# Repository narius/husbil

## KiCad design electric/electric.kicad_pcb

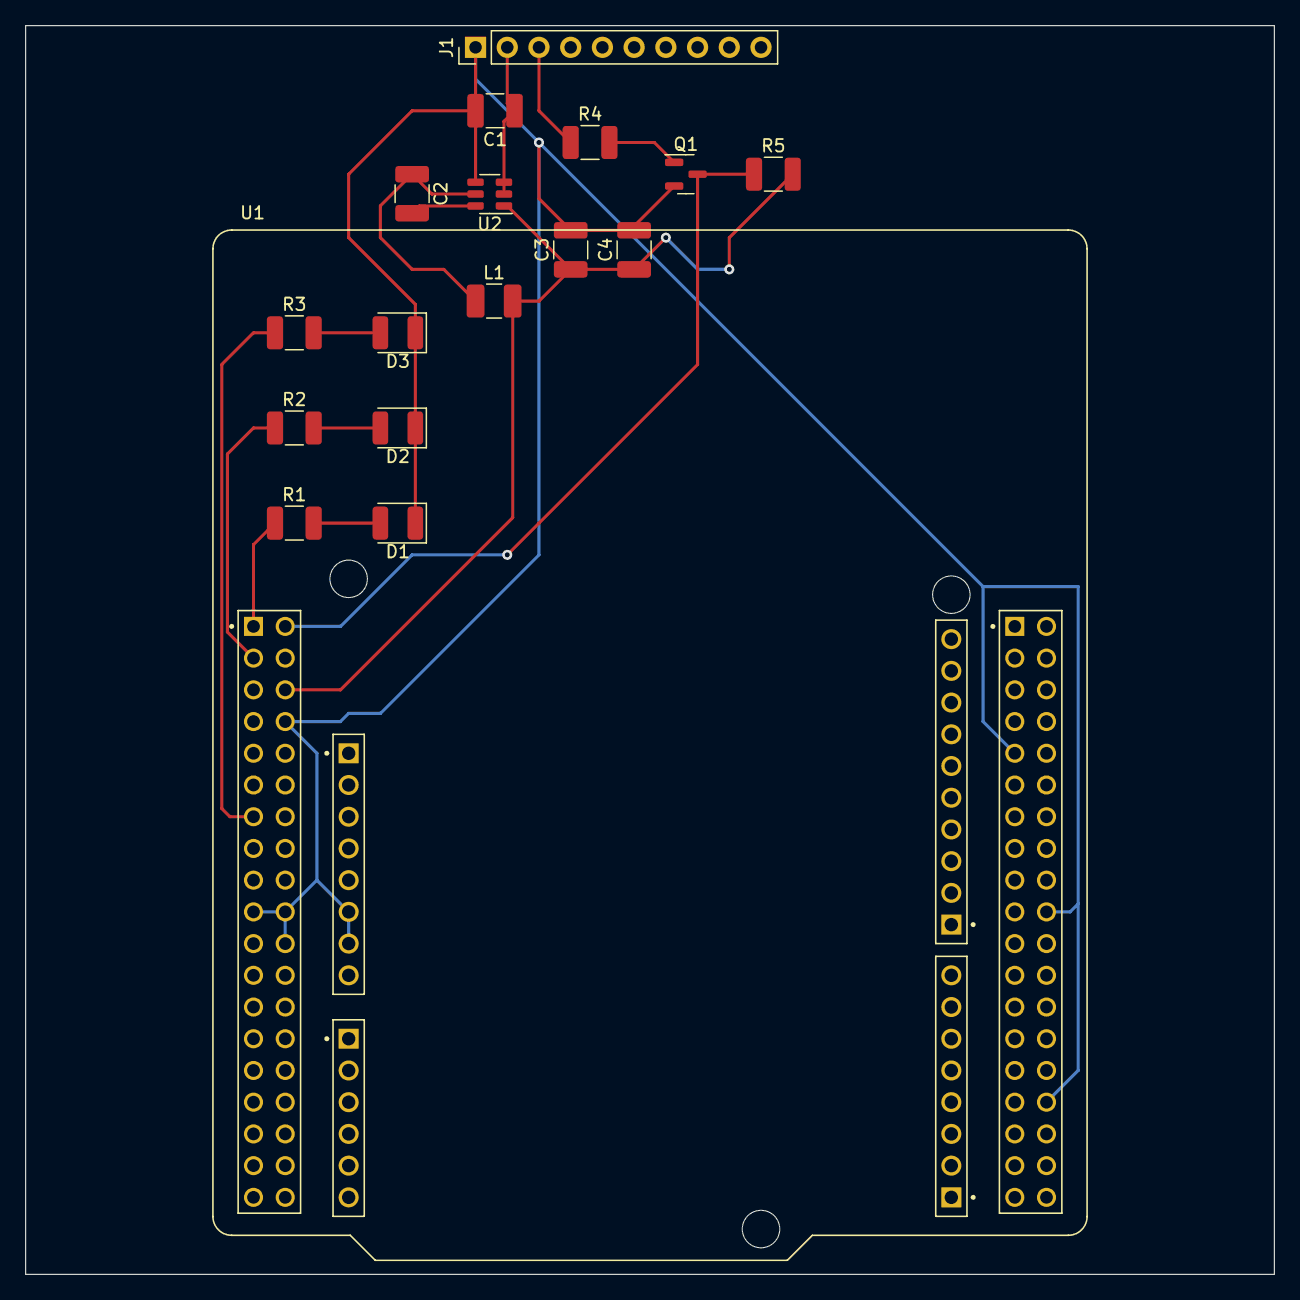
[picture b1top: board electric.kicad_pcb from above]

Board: 2 copper layers, 100.0 x 100.0 mm, 17 parts (0 on the bottom side), 14 nets.

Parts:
C1: 10uF; C_1210_3225Metric_Pad1.33x2.70mm_HandSolder
C2: 100nF; C_1210_3225Metric_Pad1.33x2.70mm_HandSolder
C3, C4: 22uF; C_1210_3225Metric_Pad1.33x2.70mm_HandSolder
D1, D2, D3: LED; LED_1210_3225Metric
J1: Screw_Terminal_01x10; PinHeader_1x10_P2.54mm_Vertical
L1: L; L_1210_3225Metric_Pad1.42x2.65mm_HandSolder
Q1: BSS138; SOT-23
R1, R2, R3, R4, R5: R; R_1210_3225Metric_Pad1.30x2.65mm_HandSolder
U1: NUCLEO-F303RE; ST_NUCLEO-F303RE
U2: AP63205WU; TSOT-23-6

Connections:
12V_IN: C1.1, J1.2, U2.2 (EN), U2.3 (IN)
E5V: C3.1, C4.1, L1.2, R5.2, U1.CN7_6 (E5V), U2.1 (FB)
GND: C1.2, C3.2, C4.2, D1.1 (K), D2.1 (K), D3.1 (K), J1.1, Q1.2 (S), U1.CN6_6 (GND), U1.CN6_7 (GND), U1.CN7_8 (GND_S1), U1.CN7_19 (GND_S1), U1.CN7_20 (GND_S1), U1.CN7_22 (GND_S1), U1.CN10_9 (GND_S2), U1.CN10_20 (GND_S2), U1.CN10_32 (AGND), U2.4 (GND)
LED1: R1.1, U1.CN7_1 (PC10)
LED2: R2.1, U1.CN7_3 (PC12)
LED3: R3.1, U1.CN7_13 (PA13)
unnamed: D1.2 (A), R1.2
unnamed: D2.2 (A), R2.2
unnamed: D3.2 (A), R3.2
unnamed: Q1.1 (G), R4.2
unnamed: C2.2, U2.6 (BST)
unnamed: C2.1, L1.1, U2.5 (SW)
VATTEN1_GPIO: Q1.3 (D), R5.1, U1.CN7_2 (PC11)
VATTEN1_INPUT(12V): J1.3, R4.1

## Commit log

2023-09-30 Intial commit
2024-04-19 Restart with RPi5
